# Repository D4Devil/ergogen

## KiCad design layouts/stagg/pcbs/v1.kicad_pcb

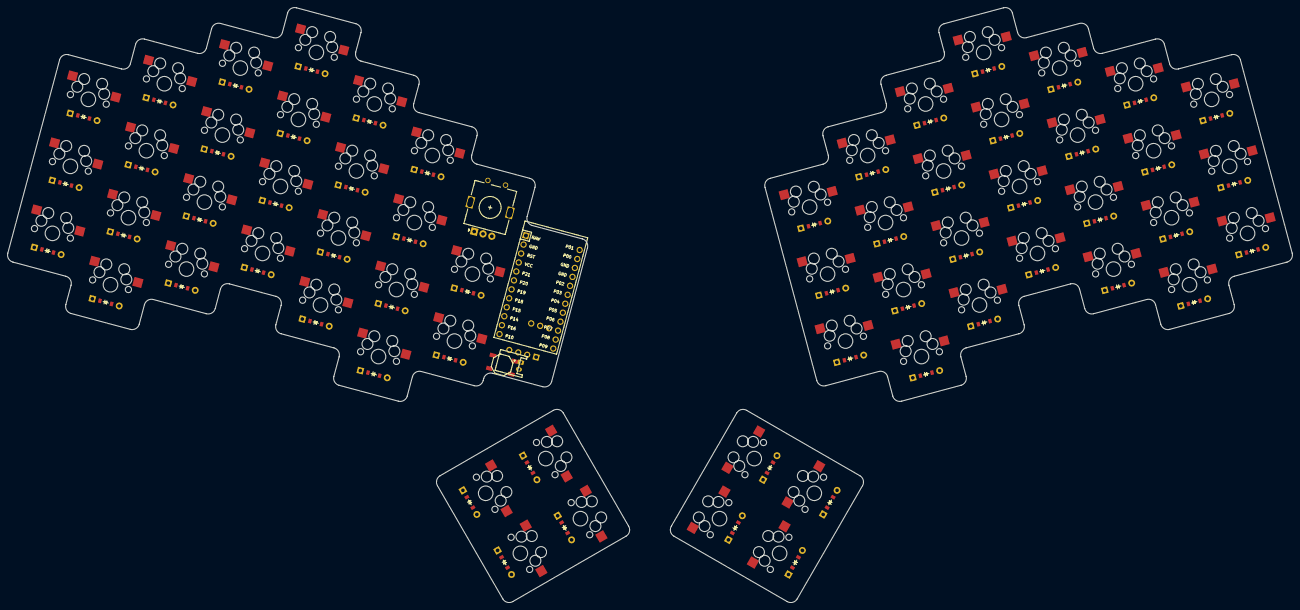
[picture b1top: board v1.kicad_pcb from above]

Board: 2 copper layers, 351.9 x 163.0 mm, 123 parts (0 on the bottom side), 65 nets, no tracks yet.

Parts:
B1: SW_TACT_ALPS_SKQGABE010
D1, D2, D3, D4, D5, D6, D7, D8, D9, D10, D11, D12, D13, D14, D15, D16, D17, D18, D19, D20, D21, D22, D23, D24, D25, D26, D27, D28, D29, D30, D31, D32, D33, D34, D35, D36, D37, D38, D39, D40, D41, D42, D43, D44, D45, D46, D47, D48, D49, D50, D51, D52, D53, D54, D55, D56, D57, D58, D59: ComboDiode
JST1: JST_PH_S2B-PH-K_02x2.00mm_Angled
MCU1: ProMicro
OLED1: OLED; OLED_headers
ROT1: rotary_encoder
S1, S2, S3, S4, S5, S6, S7, S8, S9, S10, S11, S12, S13, S14, S15, S16, S17, S18, S19, S20, S21, S22, S23, S24, S25, S26, S27, S28, S29, S30, S31, S32, S33, S34, S35, S36, S37, S38, S39, S40, S41, S42, S43, S44, S45, S46, S47, S48, S49, S50, S51, S52, S53, S54, S55, S56, S57, S58, S59: MX

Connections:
GND: B1.1, JST1.2, MCU1.2, MCU1.15, MCU1.16, OLED1.1, ROT1.B
P1: MCU1.13, ROT1.A
P2: MCU1.17, OLED1.4, ROT1.C
P3: MCU1.18, OLED1.3
RST: B1.2, MCU1.3
VCC: MCU1.4, OLED1.2
index_0_bottom: D16.2, S16.2
index_0_home: D17.2, S17.2
index_0_number: D19.2, S19.2
index_0_top: D18.2, S18.2
index_1_bottom: D20.2, S20.2
index_1_home: D21.2, S21.2
index_1_number: D23.2, S23.2
index_1_top: D22.2, S22.2
index_commands_home: D24.2, S24.2
index_commands_top: D25.2, S25.2
left_bottom: D26.2, S26.2
left_top: D27.2, S27.2
middle_bottom: D12.2, S12.2
middle_home: D13.2, S13.2
middle_number: D15.2, S15.2
middle_top: D14.2, S14.2
mirror_index_0_bottom: D45.2, S45.2
mirror_index_0_home: D46.2, S46.2
mirror_index_0_number: D48.2, S48.2
mirror_index_0_top: D47.2, S47.2
mirror_index_1_bottom: D49.2, S49.2
mirror_index_1_home: D50.2, S50.2
mirror_index_1_number: D52.2, S52.2
mirror_index_1_top: D51.2, S51.2
mirror_index_commands_home: D53.2, S53.2
mirror_index_commands_number: D55.2, S55.2
mirror_index_commands_top: D54.2, S54.2
mirror_left_bottom: D56.2, S56.2
mirror_left_top: D57.2, S57.2
mirror_middle_bottom: D41.2, S41.2
mirror_middle_home: D42.2, S42.2
mirror_middle_number: D44.2, S44.2
mirror_middle_top: D43.2, S43.2
mirror_pinkie_commands_home: D30.2, S30.2
mirror_pinkie_commands_number: D32.2, S32.2
mirror_pinkie_commands_top: D31.2, S31.2
mirror_pinky_bottom: D33.2, S33.2
mirror_pinky_home: D34.2, S34.2
mirror_pinky_number: D36.2, S36.2
mirror_pinky_top: D35.2, S35.2
mirror_right_bottom: D58.2, S58.2
mirror_right_top: D59.2, S59.2
mirror_ring_bottom: D37.2, S37.2
mirror_ring_home: D38.2, S38.2
mirror_ring_number: D40.2, S40.2
mirror_ring_top: D39.2, S39.2
pinkie_commands_home: D1.2, S1.2
pinkie_commands_number: D3.2, S3.2
pinkie_commands_top: D2.2, S2.2
pinky_bottom: D4.2, S4.2
pinky_home: D5.2, S5.2
pinky_number: D7.2, S7.2
pinky_top: D6.2, S6.2
right_bottom: D28.2, S28.2
right_top: D29.2, S29.2
ring_bottom: D8.2, S8.2
ring_home: D9.2, S9.2
ring_number: D11.2, S11.2
ring_top: D10.2, S10.2

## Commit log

2024-12-11 Hacked promicro footprint -> https://gist.github.com/rrotter/e799afdaf804c9babb882488578c9525
2024-12-11 Added stagg layout and builds
2024-12-11 added ui as submodule | removed temporary files | add nicenano footprint to yaml
